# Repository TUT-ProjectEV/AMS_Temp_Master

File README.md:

# AMS_Temp_Master

## Overview
- AMSの温度測定基板
- スレーブ側
- 2023年度10月時点で使用

## Requirement
### Development
- Kicad 7.0
### Boards
- Arduino UNO
### Libraries

## Usage
- Arduinoマイコンボードとして使用
- I2C でスレーブ側からデータ取得
- CAN の使用方法はArduino UNO で CAN BUS Shield を使用した時と同じ

## Features

## Reference
- [AMS_Temp_Master](https://github.com/ST04-tkmr/KicadProjects_EVProject/tree/main/AMS_Temp_Master) より

## Author
- Takamura
    - [GitHub](https://github.com/ST04-tkmr)

## License
- Copyright (c) 2023 東京工科大学 ProjectEV [Released under the MIT license](https://github.com/TUT-ProjectEV/AMS_Temp_Master/blob/main/LICENSE)

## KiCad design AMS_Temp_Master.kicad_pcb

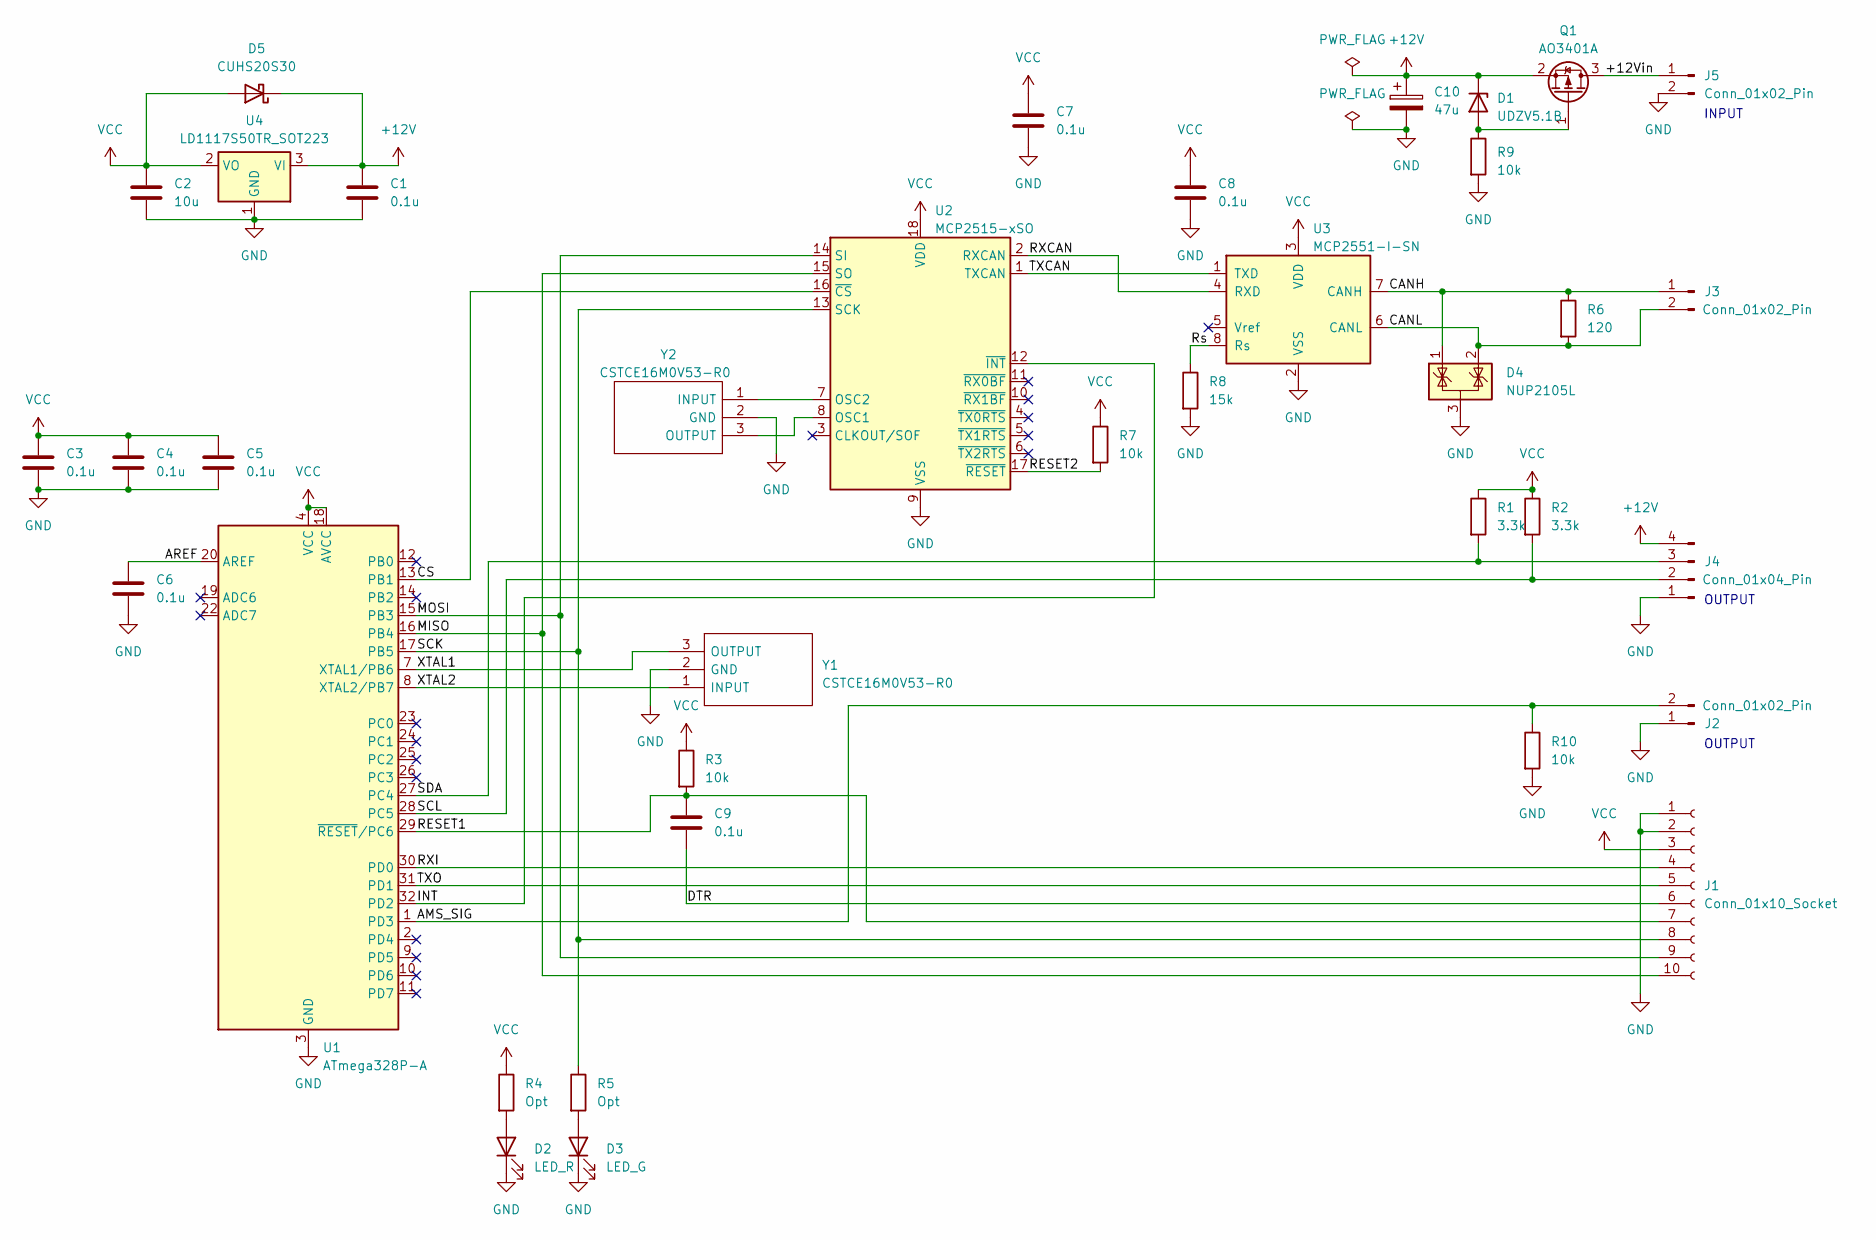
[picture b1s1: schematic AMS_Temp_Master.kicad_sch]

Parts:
C1, C3, C4, C5, C6, C7, C8, C9: 0.1u; C_0603_1608Metric
C2: 10u; C_0603_1608Metric
C10: 47u; CP_Elec_6.3x5.4_Nichicon
D1: UDZV5.1B; D_SOD-323_HandSoldering
D2: LED_R; LED_0603_1608Metric
D3: LED_G; LED_0603_1608Metric
D4: NUP2105L; SOT-23
D5: CUHS20S30; CUHS20S40H3F
J1: Conn_01x10_Socket; PinSocket_1x10_P2.54mm_Vertical
J2, J3, J5: Conn_01x02_Pin; JST_XH_S2B-XH-A_1x02_P2.50mm_Horizontal
J4: Conn_01x04_Pin; JST_XH_S4B-XH-A_1x04_P2.50mm_Horizontal
Q1: AO3401A; SOT-23
R1, R2: 3.3k; R_0603_1608Metric
R3, R7, R9, R10: 10k; R_0805_2012Metric
R4, R5: Opt; R_0603_1608Metric
R6: 120; R_0603_1608Metric
R8: 15k; R_0603_1608Metric
U1: ATmega328P-A; TQFP-32_7x7mm_P0.8mm
U2: MCP2515-xSO; SOIC-18W_7.5x11.6mm_P1.27mm
U3: MCP2551-I-SN; SOIC-8_3.9x4.9mm_P1.27mm
U4: LD1117S50TR_SOT223; SOT-223-3_TabPin2
Y1, Y2: CSTCE16M0V53-R0; CSTCE16M0V53R0; Manufacturer_Part_Number CSTCE16M0V53-R0; Mouser Part Number 81-CSTCE16M0V53-R0

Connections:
+12V: C1.1, C10.1, D1.1 (K), D5.1 (K), J4.4, Q1.2 (S), U4.3 (VI)
/+12Vin: J5.1, Q1.3 (D)
/AMS_SIG: J2.2, R10.1, U1.1 (PD3)
/AREF: C6.1, U1.20 (AREF)
/CANH: D4.1 (K), J3.1, R6.1, U3.7 (CANH)
/CANL: D4.2 (K), J3.2, R6.2, U3.6 (CANL)
/CS: U1.13 (PB1), U2.16 (~CS)
/DTR: C9.2, J1.6
/INT: U1.32 (PD2), U2.12 (~INT)
/MISO: J1.10, U1.16 (PB4), U2.15 (SO)
/MOSI: J1.9, U1.15 (PB3), U2.14 (SI)
/RESET1: C9.1, J1.7, R3.2, U1.29 (~RESET/PC6)
/RESET2: R7.2, U2.17 (~RESET)
/RXCAN: U2.2 (RXCAN), U3.4 (RXD)
/RXI: J1.4, U1.30 (PD0)
/Rs: R8.1, U3.8 (Rs)
/SCK: J1.8, R5.1, U1.17 (PB5), U2.13 (SCK)
/SCL: J4.2, R2.2, U1.28 (PC5)
/SDA: J4.3, R1.2, U1.27 (PC4)
/TXCAN: U2.1 (TXCAN), U3.1 (TXD)
/TXO: J1.5, U1.31 (PD1)
/XTAL1: U1.7 (XTAL1/PB6), Y1.3 (OUTPUT)
/XTAL2: U1.8 (XTAL2/PB7), Y1.1 (INPUT)
GND: C1.2, C2.2, C3.2, C4.2, C5.2, C6.2, C7.2, C8.2, C10.2, D2.1 (K), D3.1 (K), D4.3 (A), J1.1, J1.2, J2.1, J4.1, J5.2, R8.2, R9.2, R10.2, U1.3 (GND), U1.5 (GND), U1.21 (GND), U2.9 (VSS), U3.2 (VSS), U4.1 (GND), Y1.2 (GND), Y2.2 (GND)
unnamed: D1.2 (A), Q1.1 (G), R9.1
unnamed: D2.2 (A), R4.2
unnamed: D3.2 (A), R5.2
unnamed: U2.8 (OSC1), Y2.3 (OUTPUT)
unnamed: U2.7 (OSC2), Y2.1 (INPUT)
VCC: C2.1, C3.1, C4.1, C5.1, C7.1, C8.1, D5.2 (A), J1.3, R1.1, R2.1, R3.1, R4.1, R7.1, U1.4 (VCC), U1.6 (VCC), U1.18 (AVCC), U2.18 (VDD), U3.3 (VDD), U4.2 (VO)

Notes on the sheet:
OUTPUT
INPUT

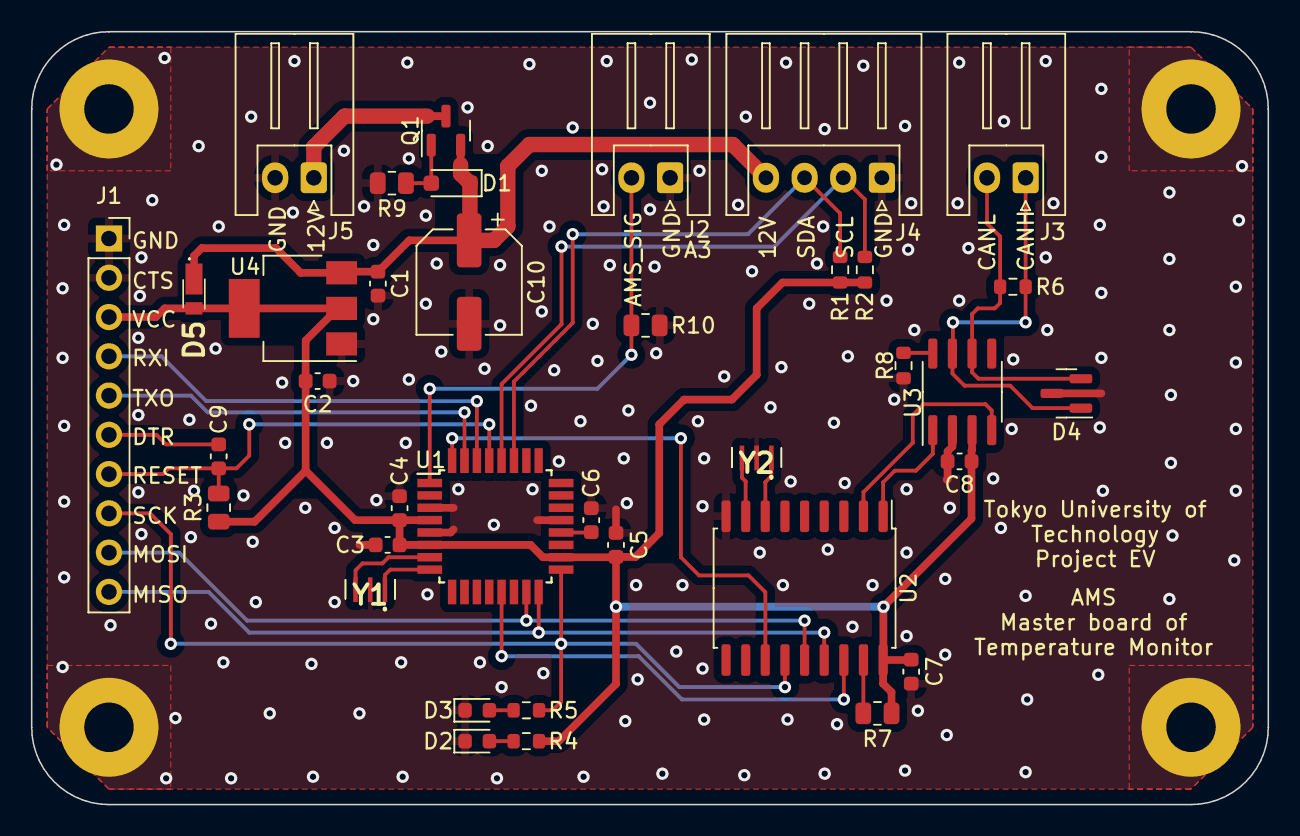
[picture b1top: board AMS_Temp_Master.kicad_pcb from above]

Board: 2 copper layers, 80.0 x 50.0 mm, 37 parts (0 on the bottom side), 30 nets.

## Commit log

2023-10-22 add project
